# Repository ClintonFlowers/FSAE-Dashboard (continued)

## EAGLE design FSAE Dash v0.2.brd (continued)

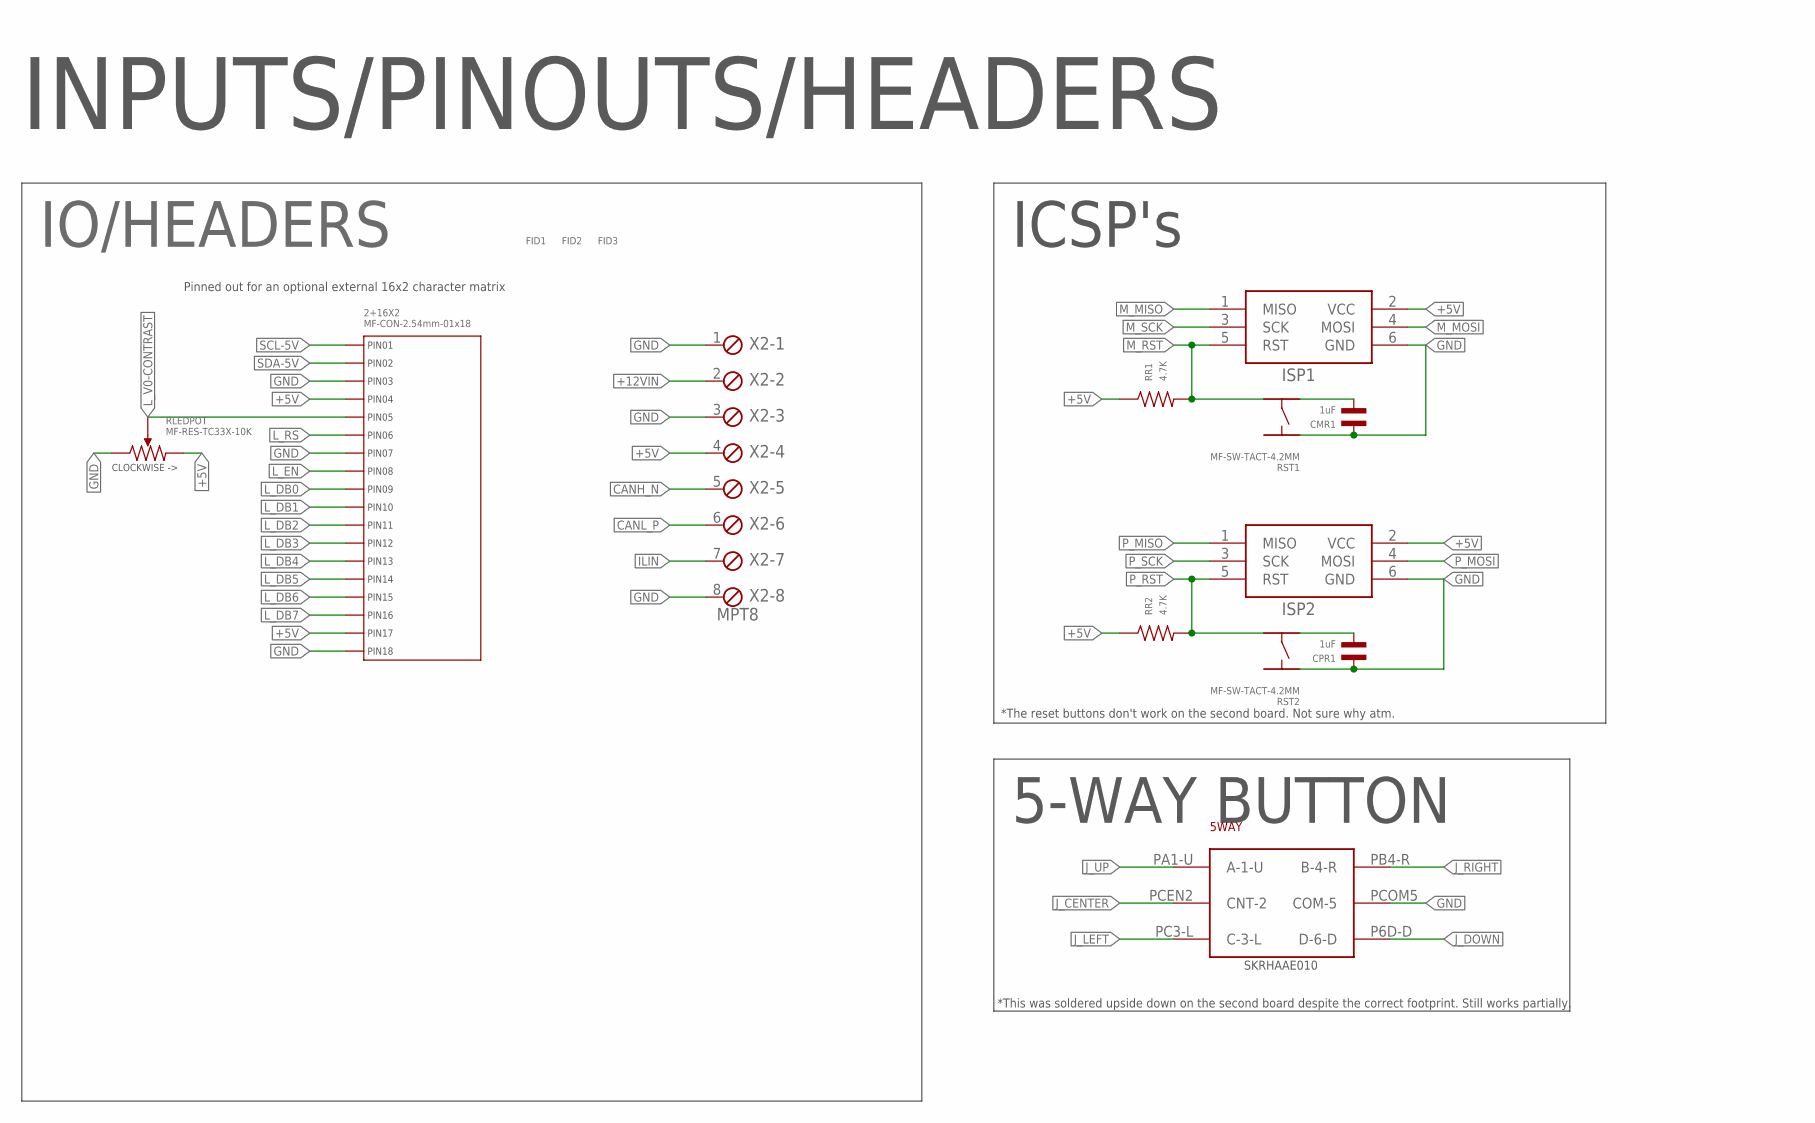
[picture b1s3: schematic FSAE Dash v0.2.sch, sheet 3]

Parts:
2+16X2: MF-CON-2.54mm-01x18; PTH_2.54MM_01X18
5WAY: SKRHAAE010; ALPS-SKRHAAE010
CMR1: 1uF; C0402
CPR1: 1uF; C0402
FID1, FID2, FID3: FIDUCIAL_100MIL
ISP1, ISP2: AVRISP-6; AVRISP
RLEDPOT: MF-RES-TC33X-10K; TC33
RR1, RR2: 4.7K; R0603
RST1, RST2: MF-SW-TACT-4.2MM; TACT4.2MM
X2: MPT8; 8POL254

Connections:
+5V: 2+16X2.P$4 (PIN4), 2+16X2.P$17 (PIN17), ISP1.2 (VCC), ISP2.2 (VCC), RLEDPOT.P$3, RR1.P$1, RR2.P$1, X2.4; also elsewhere on the board
+12VIN: X2.2; also elsewhere on the board
CANH_N: X2.5; also elsewhere on the board
CANL_P: X2.6; also elsewhere on the board
GND: 2+16X2.P$3 (PIN3), 2+16X2.P$7 (PIN7), 2+16X2.P$18 (PIN18), 5WAY.PCOM5 (COM-5), CMR1.P$1, CPR1.P$1, ISP1.6 (GND), ISP2.6 (GND), RLEDPOT.P$1, RST1.P$1, RST2.P$1, X2.1, X2.3, X2.8; also elsewhere on the board
ILIN: X2.7; also elsewhere on the board
J_CENTER: 5WAY.PCEN2 (CNT-2); also elsewhere on the board
J_DOWN: 5WAY.P6D-D (D-6-D); also elsewhere on the board
J_LEFT: 5WAY.PC3-L (C-3-L); also elsewhere on the board
J_RIGHT: 5WAY.PB4-R (B-4-R); also elsewhere on the board
J_UP: 5WAY.PA1-U (A-1-U); also elsewhere on the board
L_DB0: 2+16X2.P$9 (PIN9); also elsewhere on the board
L_DB1: 2+16X2.P$10 (PIN10); also elsewhere on the board
L_DB2: 2+16X2.P$11 (PIN11); also elsewhere on the board
L_DB3: 2+16X2.P$12 (PIN12); also elsewhere on the board
L_DB4: 2+16X2.P$13 (PIN13); also elsewhere on the board
L_DB5: 2+16X2.P$14 (PIN14); also elsewhere on the board
L_DB6: 2+16X2.P$15 (PIN15); also elsewhere on the board
L_DB7: 2+16X2.P$16 (PIN16); also elsewhere on the board
L_EN: 2+16X2.P$8 (PIN8); also elsewhere on the board
L_RS: 2+16X2.P$6 (PIN6); also elsewhere on the board
L_V0-CONTRAST: 2+16X2.P$5 (PIN5), RLEDPOT.P$2
M_MISO: ISP1.1 (MISO); also elsewhere on the board
M_MOSI: ISP1.4 (MOSI); also elsewhere on the board
M_RST: ISP1.5 (RST), RR1.P$2, RST1.P$4; also elsewhere on the board
M_SCK: ISP1.3 (SCK); also elsewhere on the board
unnamed: CPR1.P$2, RST2.P$3
unnamed: CMR1.P$2, RST1.P$3
P_MISO: ISP2.1 (MISO); also elsewhere on the board
P_MOSI: ISP2.4 (MOSI); also elsewhere on the board
P_RST: ISP2.5 (RST), RR2.P$2, RST2.P$4; also elsewhere on the board
P_SCK: ISP2.3 (SCK); also elsewhere on the board
SCL-5V: 2+16X2.P$1 (PIN1); also elsewhere on the board
SDA-5V: 2+16X2.P$2 (PIN2); also elsewhere on the board

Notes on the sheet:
IO/HEADERS
ICSP's
INPUTS/PINOUTS/HEADERS
5-WAY BUTTON
Pinned out for an optional external 16x2 character matrix
SKRHAAE010
*The reset buttons don't work on the second board. Not sure why atm.
*This was soldered upside down on the second board despite the correct footprint. Still works partially.

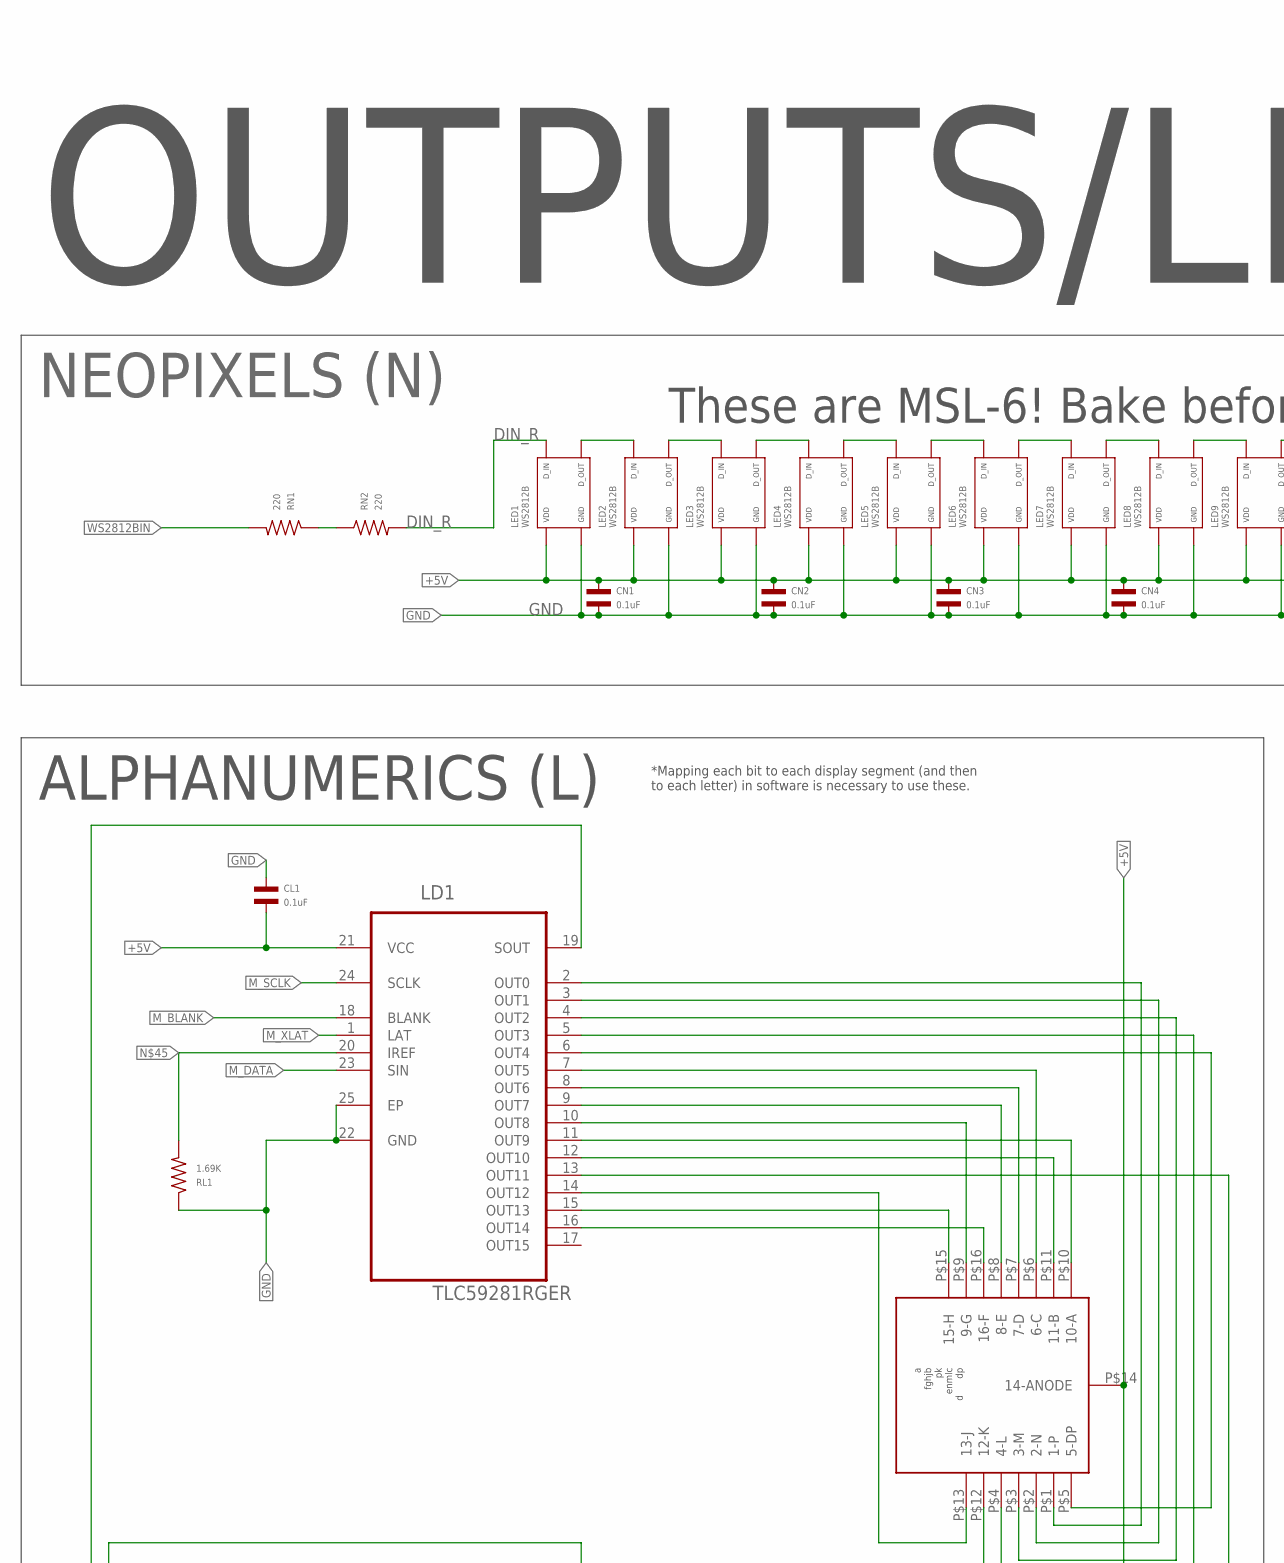
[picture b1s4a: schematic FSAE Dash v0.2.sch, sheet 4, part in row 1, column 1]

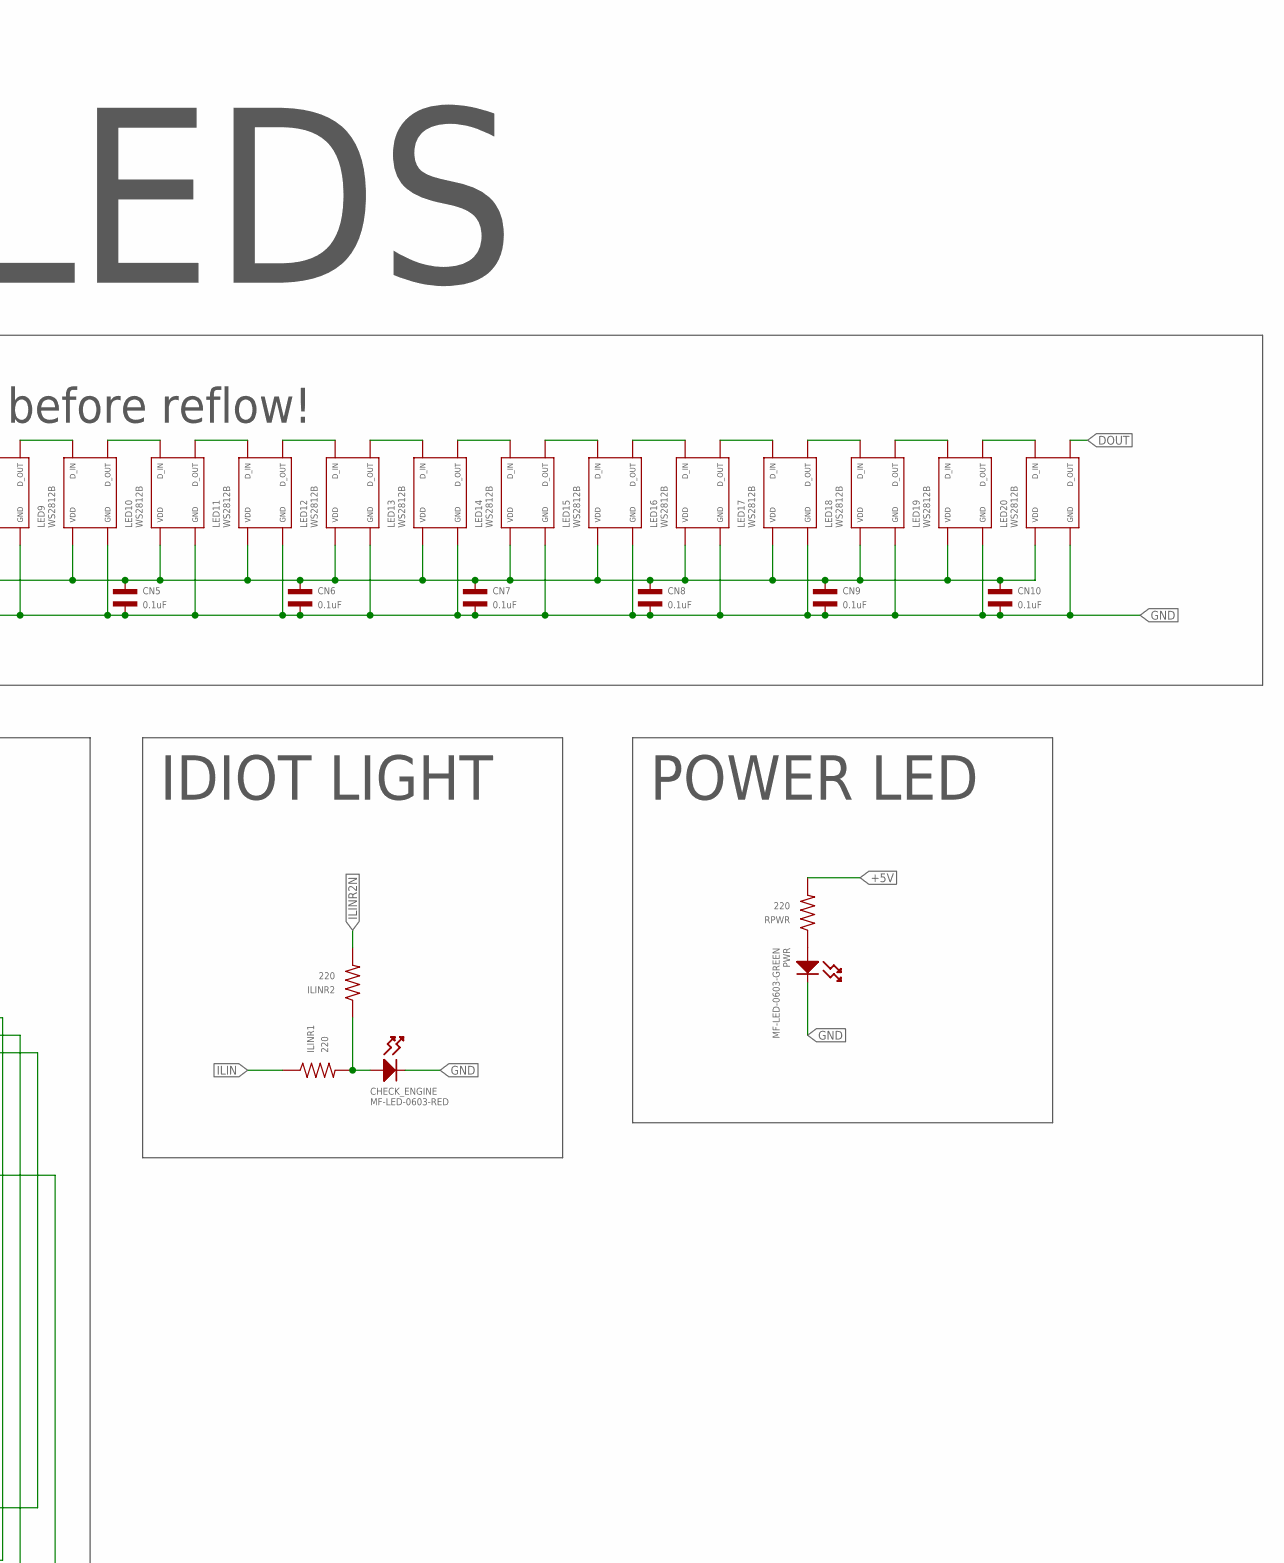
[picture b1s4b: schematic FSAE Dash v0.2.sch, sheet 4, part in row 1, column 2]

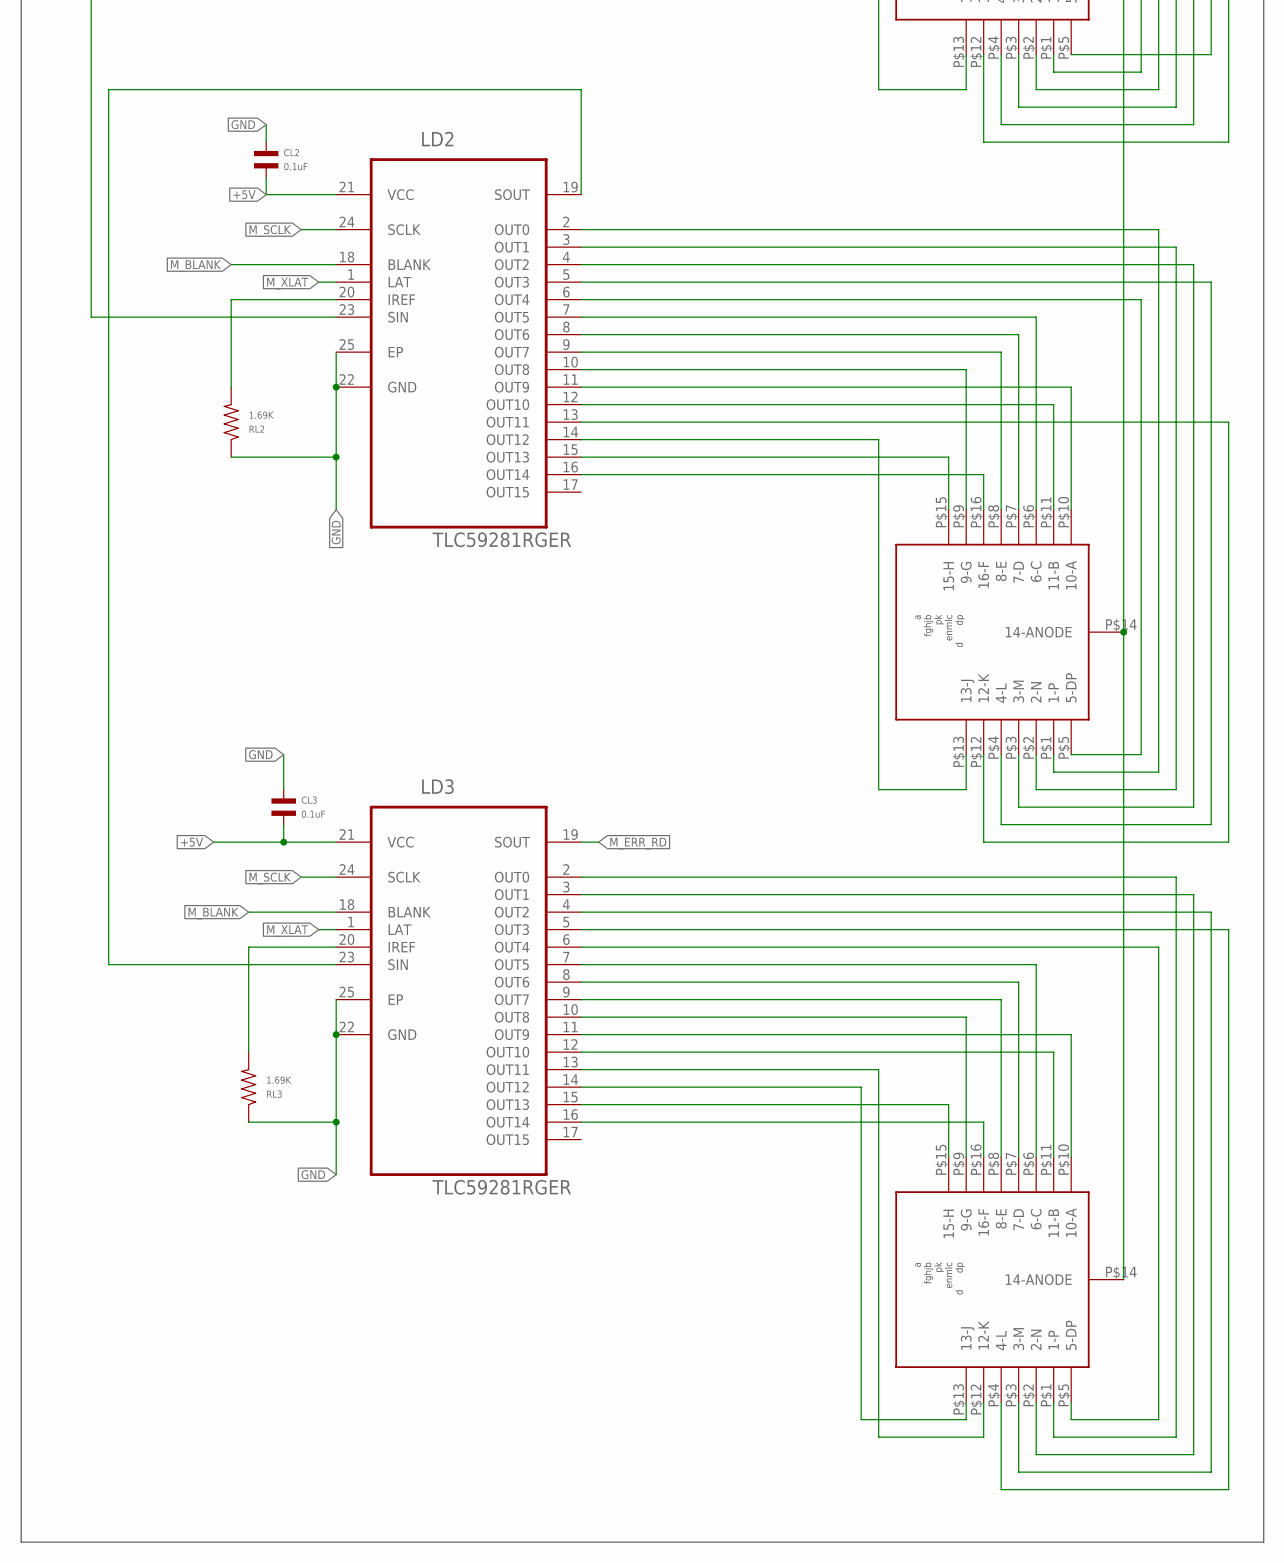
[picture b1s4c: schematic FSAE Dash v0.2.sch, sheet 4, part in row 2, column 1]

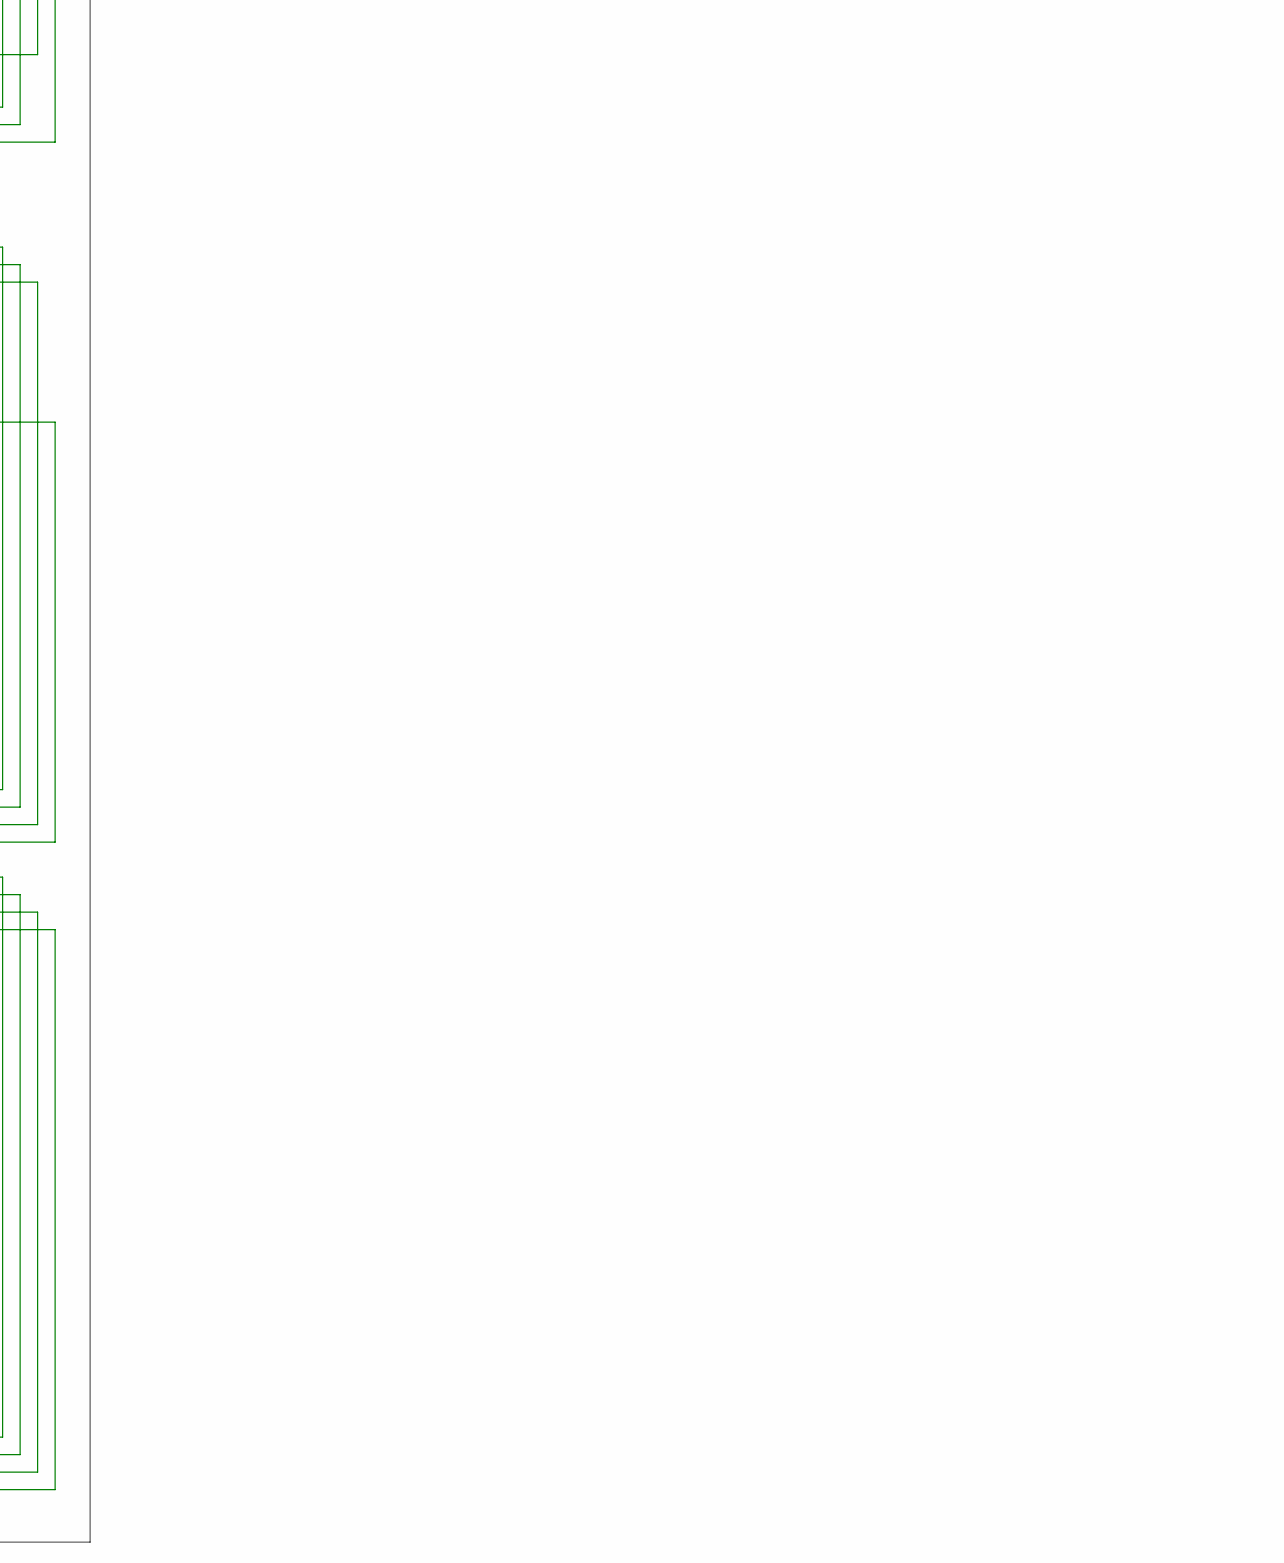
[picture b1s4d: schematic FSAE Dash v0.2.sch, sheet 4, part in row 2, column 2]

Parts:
CHECK_ENGINE: MF-LED-0603-RED; LED0603
CL1, CL2, CL3: 0.1uF; C0402
CN1, CN2, CN3, CN4, CN5, CN6, CN7, CN8, CN9, CN10: 0.1uF; C0402
ILINR1, ILINR2: 220; R0402
L1, L2, L3: ACPSA04-41SYKWA
LD1, LD2, LD3: TLC59281RGER; QFN50P400X400X100-25N
LED1, LED2, LED3, LED4, LED5, LED6, LED7, LED8, LED9, LED10, LED11, LED12, LED13, LED14, LED15, LED16, LED17, LED18, LED19, LED20: WS2812B
PWR: MF-LED-0603-GREEN; LED0603
RL1, RL2, RL3: 1.69K; R0603
RN1, RN2: 220; R0402
RPWR: 220; R0402

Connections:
+5V: CL1.P$2, CL2.P$2, CL3.P$2, CN1.P$1, CN2.P$1, CN3.P$1, CN4.P$1, CN5.P$1, CN6.P$1, CN7.P$1, CN8.P$1, CN9.P$1, CN10.P$1, L1.P$14 (14-ANODE), L2.P$14 (14-ANODE), L3.P$14 (14-ANODE), LD1.21 (VCC), LD2.21 (VCC), LD3.21 (VCC), LED1.P$1 (VDD), LED2.P$1 (VDD), LED3.P$1 (VDD), LED4.P$1 (VDD), LED5.P$1 (VDD), LED6.P$1 (VDD), LED7.P$1 (VDD), LED8.P$1 (VDD), LED9.P$1 (VDD), LED10.P$1 (VDD), LED11.P$1 (VDD), LED12.P$1 (VDD), LED13.P$1 (VDD), LED14.P$1 (VDD), LED15.P$1 (VDD), LED16.P$1 (VDD), LED17.P$1 (VDD), LED18.P$1 (VDD), LED19.P$1 (VDD), LED20.P$1 (VDD), RPWR.P$2; also elsewhere on the board
DIN_R: LED1.P$4 (DIN), RN2.P$2
DOUT: LED20.P$2 (DOUT)
GND: CHECK_ENGINE.CATHODE, CL1.P$1, CL2.P$1, CL3.P$1, CN1.P$2, CN2.P$2, CN3.P$2, CN4.P$2, CN5.P$2, CN6.P$2, CN7.P$2, CN8.P$2, CN9.P$2, CN10.P$2, LD1.22 (GND), LD1.25 (EP), LD2.22 (GND), LD2.25 (EP), LD3.22 (GND), LD3.25 (EP), LED1.P$3 (VSS), LED2.P$3 (VSS), LED3.P$3 (VSS), LED4.P$3 (VSS), LED5.P$3 (VSS), LED6.P$3 (VSS), LED7.P$3 (VSS), LED8.P$3 (VSS), LED9.P$3 (VSS), LED10.P$3 (VSS), LED11.P$3 (VSS), LED12.P$3 (VSS), LED13.P$3 (VSS), LED14.P$3 (VSS), LED15.P$3 (VSS), LED16.P$3 (VSS), LED17.P$3 (VSS), LED18.P$3 (VSS), LED19.P$3 (VSS), LED20.P$3 (VSS), PWR.CATHODE, RL1.P$1, RL2.P$1, RL3.P$1; also elsewhere on the board
ILIN: ILINR1.P$1; also elsewhere on the board
ILINR2N: ILINR2.P$2; also elsewhere on the board
M_BLANK: LD1.18 (BLANK), LD2.18 (BLANK), LD3.18 (BLANK); also elsewhere on the board
M_DATA: LD1.23 (SIN); also elsewhere on the board
M_ERR_RD: LD3.19 (SOUT); also elsewhere on the board
M_SCLK: LD1.24 (SCLK), LD2.24 (SCLK), LD3.24 (SCLK); also elsewhere on the board
M_XLAT: LD1.1 (LAT), LD2.1 (LAT), LD3.1 (LAT); also elsewhere on the board
unnamed: LED1.P$2 (DOUT), LED2.P$4 (DIN)
unnamed: LED2.P$2 (DOUT), LED3.P$4 (DIN)
unnamed: LED3.P$2 (DOUT), LED4.P$4 (DIN)
unnamed: LED4.P$2 (DOUT), LED5.P$4 (DIN)
unnamed: LED5.P$2 (DOUT), LED6.P$4 (DIN)
unnamed: LED6.P$2 (DOUT), LED7.P$4 (DIN)
unnamed: LED7.P$2 (DOUT), LED8.P$4 (DIN)
unnamed: PWR.ANODE, RPWR.P$1
unnamed: LED8.P$2 (DOUT), LED9.P$4 (DIN)
unnamed: LED9.P$2 (DOUT), LED10.P$4 (DIN)
unnamed: LED10.P$2 (DOUT), LED11.P$4 (DIN)
unnamed: LED11.P$2 (DOUT), LED12.P$4 (DIN)
unnamed: LED12.P$2 (DOUT), LED13.P$4 (DIN)
unnamed: LED13.P$2 (DOUT), LED14.P$4 (DIN)
unnamed: LED14.P$2 (DOUT), LED15.P$4 (DIN)
unnamed: LED15.P$2 (DOUT), LED16.P$4 (DIN)
unnamed: LED16.P$2 (DOUT), LED17.P$4 (DIN)
unnamed: LED17.P$2 (DOUT), LED18.P$4 (DIN)
unnamed: LED18.P$2 (DOUT), LED19.P$4 (DIN)
unnamed: LED19.P$2 (DOUT), LED20.P$4 (DIN)
unnamed: CHECK_ENGINE.ANODE, ILINR1.P$2, ILINR2.P$1
unnamed: RN1.P$1, RN2.P$1
unnamed: LD1.20 (IREF), RL1.P$2
unnamed: LD1.19 (SOUT), LD2.23 (SIN)
unnamed: L3.P$1 (1-P), LD3.2 (OUT0)
unnamed: LD2.20 (IREF), RL2.P$2
unnamed: LD2.19 (SOUT), LD3.23 (SIN)
unnamed: LD3.20 (IREF), RL3.P$2
unnamed: L3.P$2 (2-N), LD3.3 (OUT1)
unnamed: L3.P$3 (3-M), LD3.4 (OUT2)
unnamed: L3.P$4 (4-L), LD3.5 (OUT3)
unnamed: L3.P$5 (5-DP), LD3.6 (OUT4)
unnamed: L3.P$6 (6-C), LD3.7 (OUT5)
unnamed: L3.P$7 (7-D), LD3.8 (OUT6)
unnamed: L3.P$8 (8-E), LD3.9 (OUT7)
unnamed: L3.P$9 (9-G), LD3.10 (OUT8)
unnamed: L3.P$10 (10-A), LD3.11 (OUT9)
unnamed: L3.P$11 (11-B), LD3.12 (OUT10)
unnamed: L3.P$12 (12-K), LD3.13 (OUT11)
unnamed: L3.P$13 (13-J), LD3.14 (OUT12)
unnamed: L3.P$15 (15-H), LD3.15 (OUT13)
unnamed: L3.P$16 (16-F), LD3.16 (OUT14)
unnamed: L2.P$1 (1-P), LD2.2 (OUT0)
unnamed: L2.P$2 (2-N), LD2.3 (OUT1)
unnamed: L2.P$3 (3-M), LD2.4 (OUT2)
unnamed: L2.P$4 (4-L), LD2.5 (OUT3)
unnamed: L2.P$5 (5-DP), LD2.6 (OUT4)
unnamed: L2.P$6 (6-C), LD2.7 (OUT5)
unnamed: L2.P$7 (7-D), LD2.8 (OUT6)
unnamed: L2.P$8 (8-E), LD2.9 (OUT7)
unnamed: L2.P$9 (9-G), LD2.10 (OUT8)
unnamed: L2.P$10 (10-A), LD2.11 (OUT9)
unnamed: L2.P$11 (11-B), LD2.12 (OUT10)
unnamed: L2.P$12 (12-K), LD2.13 (OUT11)
unnamed: L2.P$13 (13-J), LD2.14 (OUT12)
unnamed: L2.P$15 (15-H), LD2.15 (OUT13)
unnamed: L2.P$16 (16-F), LD2.16 (OUT14)
unnamed: L1.P$1 (1-P), LD1.2 (OUT0)
unnamed: L1.P$2 (2-N), LD1.3 (OUT1)
unnamed: L1.P$3 (3-M), LD1.4 (OUT2)
unnamed: L1.P$4 (4-L), LD1.5 (OUT3)
unnamed: L1.P$5 (5-DP), LD1.6 (OUT4)
unnamed: L1.P$6 (6-C), LD1.7 (OUT5)
unnamed: L1.P$7 (7-D), LD1.8 (OUT6)
unnamed: L1.P$8 (8-E), LD1.9 (OUT7)
unnamed: L1.P$9 (9-G), LD1.10 (OUT8)
unnamed: L1.P$10 (10-A), LD1.11 (OUT9)
unnamed: L1.P$11 (11-B), LD1.12 (OUT10)
unnamed: L1.P$12 (12-K), LD1.13 (OUT11)
unnamed: L1.P$13 (13-J), LD1.14 (OUT12)
unnamed: L1.P$15 (15-H), LD1.15 (OUT13)
unnamed: L1.P$16 (16-F), LD1.16 (OUT14)
WS2812BIN: RN1.P$2; also elsewhere on the board

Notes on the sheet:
ALPHANUMERICS (L)
IDIOT LIGHT
POWER LED
NEOPIXELS (N)
OUTPUTS/LEDS
These are MSL-6! Bake before reflow!
*Mapping each bit to each display segment (and then to each letter) in software is necessary to use these.

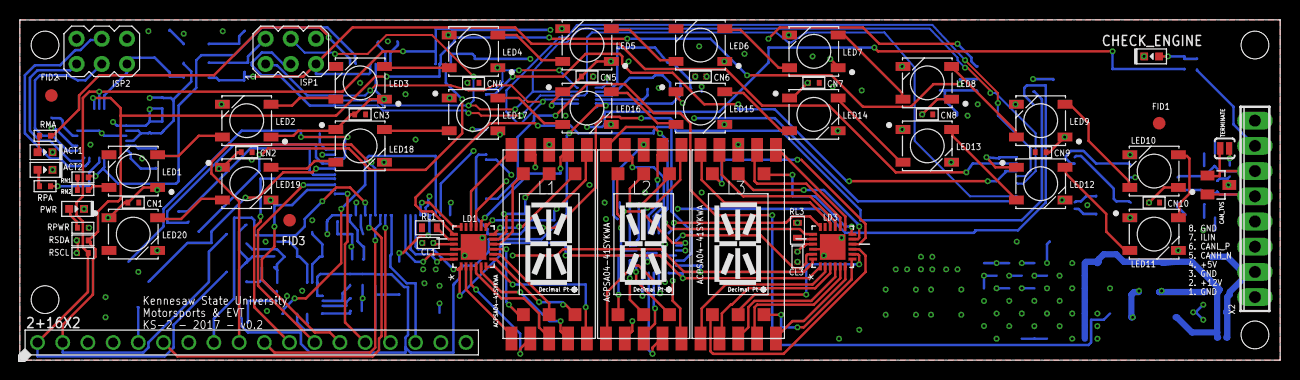
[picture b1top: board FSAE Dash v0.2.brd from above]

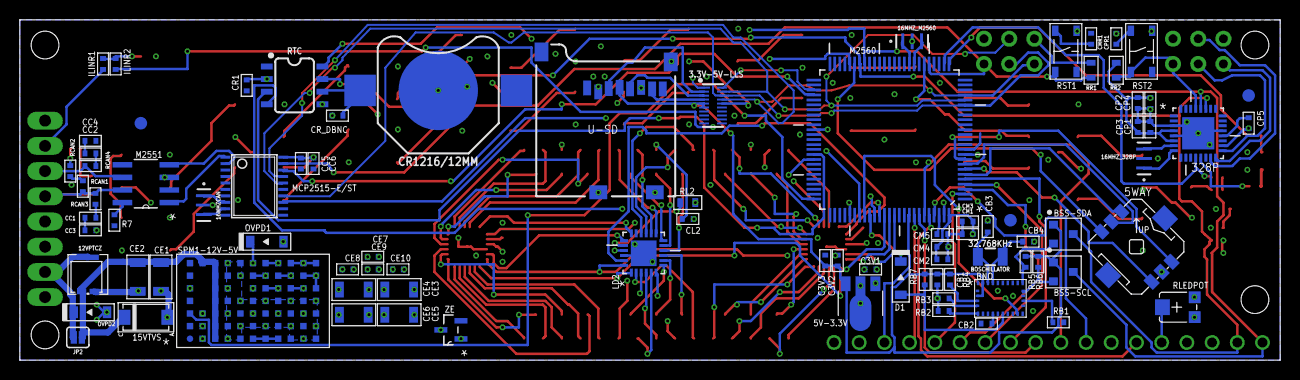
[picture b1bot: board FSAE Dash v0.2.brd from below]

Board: 4 copper layers, 127.0 x 34.3 mm, 143 parts (84 on the bottom side), 161 nets.

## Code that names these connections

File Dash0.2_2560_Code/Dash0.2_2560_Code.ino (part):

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// Pin definitions specific to how the MCP2515 is wired up.
// If this code is being breadboarded off of the actual PCB: Pin 10 for SparkFun canbus shield
#define CS_PIN    36
#define CAN_INT_PIN   18 // INTERRUPT != PIN. 
/* 
 Board  int.0 int.1 int.2 int.3 int.4 int.5
 Uno, Ethernet  2 3        
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const int dataPin = 62;
// Pins for the joystick on the rear of the device, accounting for improper hardware placement. Unused in current code.
const int centerPin = PE6;  // Center in schematic, J_Common as installed. 
const int rightPin = 19;    // J_Left in schematic
const int leftPin = PE7;    // J_Right in schematic
const int downPin = 2;      // J_Up in schematic
const int upPin = 3;        // J_Down in schematic
// How many (14-segment + dp) alphanumeric displays are connected
const int numberOfAlphanumerics = 3;
// Vars for data passed to shifting function
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  delay(100);

  // CAN Interrupt setup and CAN stuff
  pinMode(CAN_INT_PIN, INPUT_PULLUP); // Maybe not necessary, but shouldn't hurt
  attachInterrupt(digitalPinToInterrupt(CAN_INT_PIN), ISR_can, FALLING);
  for(int i = 0; i < 3; i++){
    MS_Parse();
    delay(1);
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
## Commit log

2017-07-01 :neckbeard: Added .gitattributes & .gitignore files
2017-07-01 Initial Commit
    Initial .SCH, .BRD, .PDF, Readme, and enclosure .STL's and .SLDPRT's
2017-07-01 Updated .gitattributes & .gitignore files
    Removing unnecessary autogenerated neckbeard emoji
2017-07-01 Attaching Image and License, fixing Readme
2018-03-21 Added code
    Added the current code for both microcontrollers
2018-03-21 Updating Footprint and Enclosure Model
2018-04-03 Minor code fixes; Updated readme
2018-04-03 Fixed typo
2019-05-21 Updating Eagle library
2019-06-15 Initial KS3E dash commit
2019-06-16 Progress towards KS3E functionality
2019-10-01 Updating my library and adding class stuff
